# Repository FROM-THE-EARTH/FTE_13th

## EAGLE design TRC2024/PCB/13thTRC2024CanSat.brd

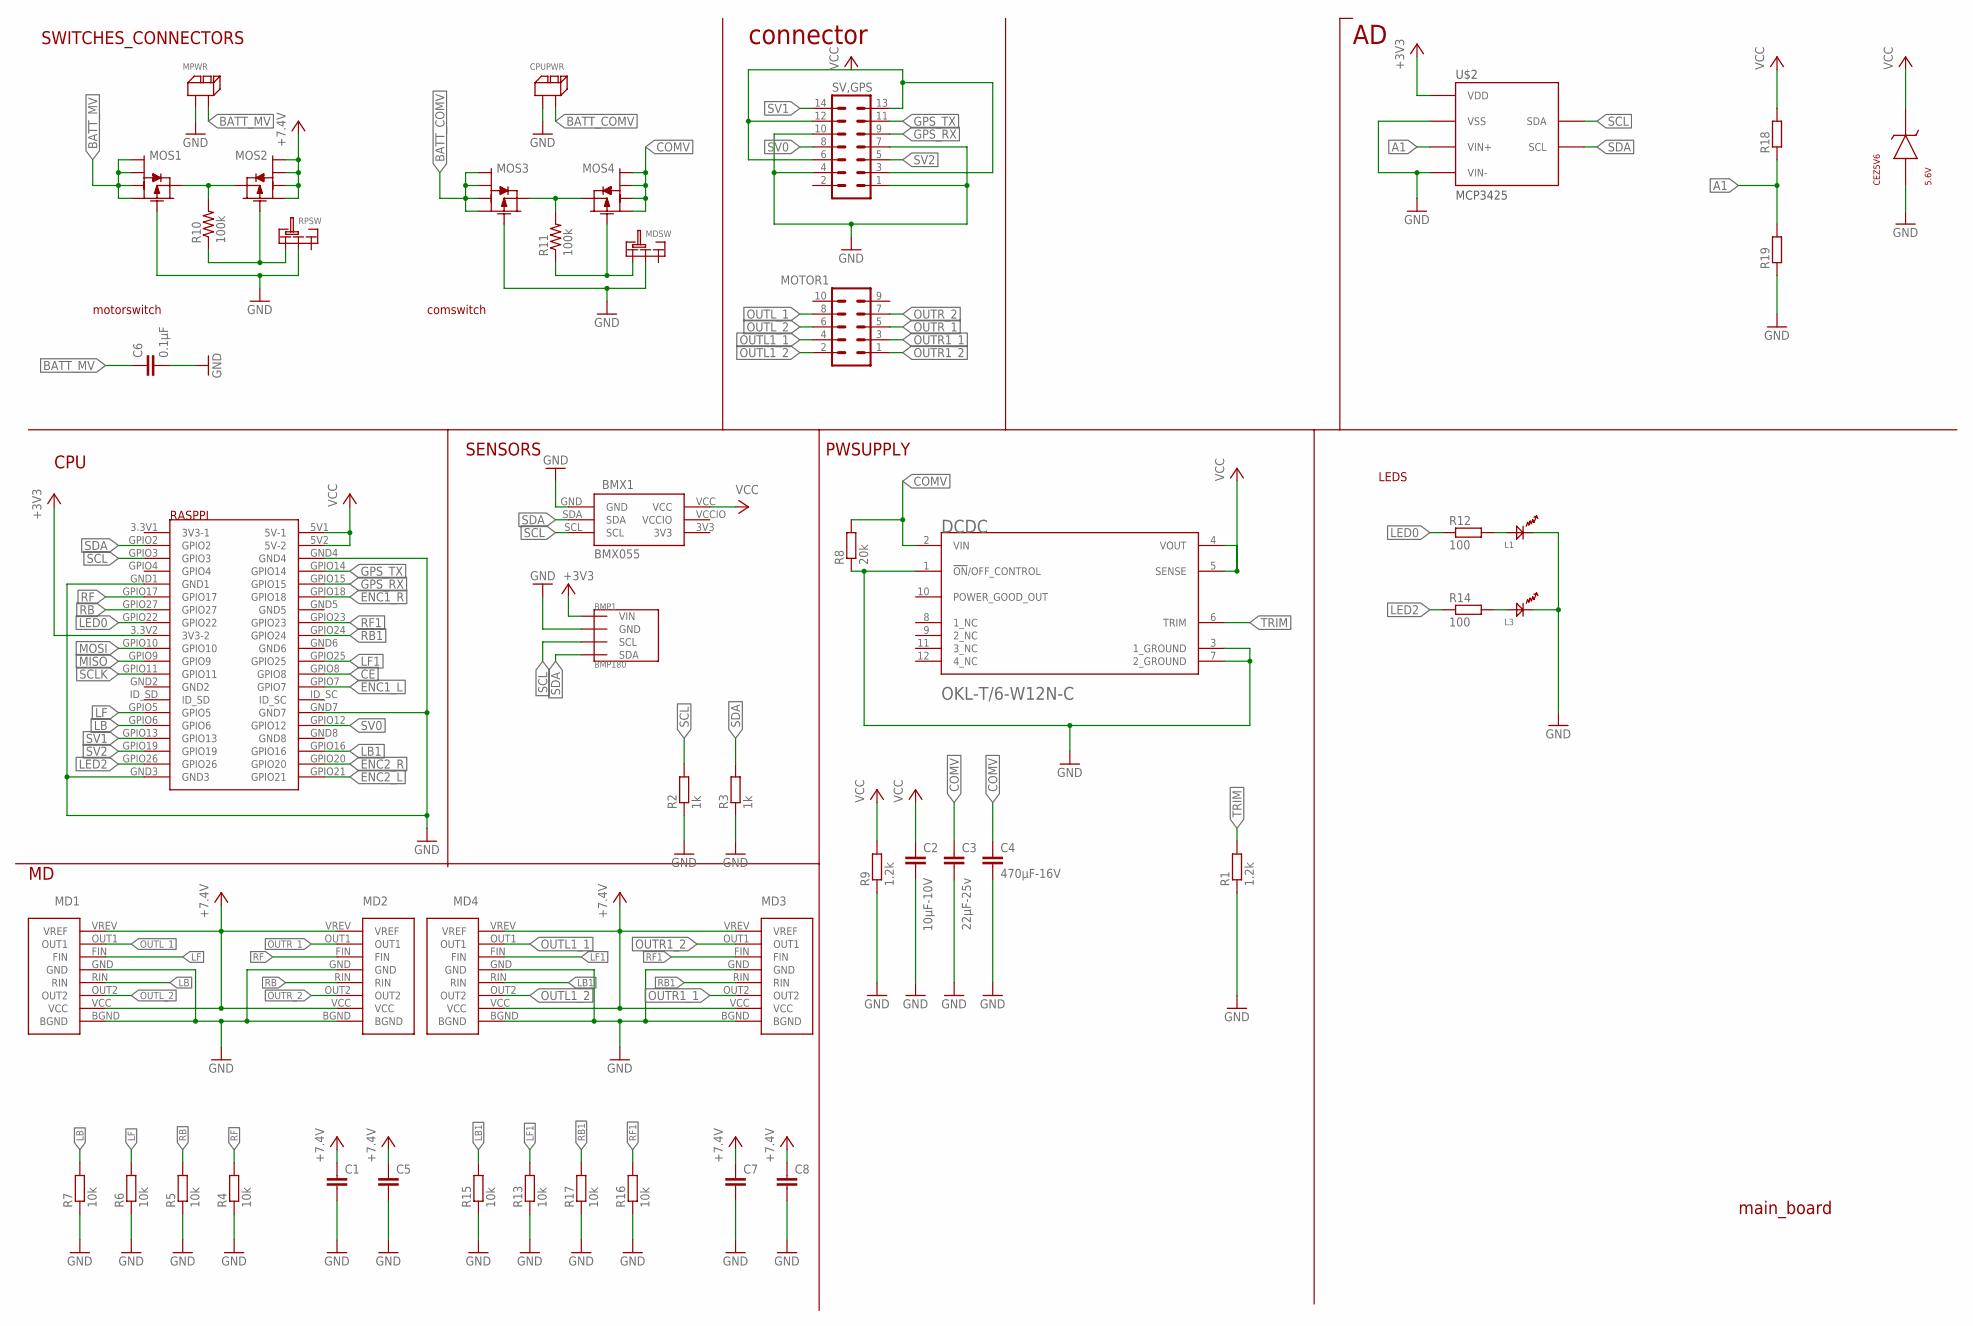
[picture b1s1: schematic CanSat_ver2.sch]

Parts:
BMP1: BMP180; GY-68
BMX1: BMX055
C1, C5, C7, C8: C-EUC0603; C0603
C2: 10μF-10V; C0603
C3: 22μF-25v; C0805
C4: 470μF-16V; C0603
C6: 0.1μF; C0603
CEZ5V6: 5.6V; CEZ5V6
CPUPWR: 2PIN
DCDC: OKL-T/6-W12N-CMURATA_OKL-T-6-W12N-C_0_0; MURATA_OKL-T-6-W12N-C_0
L1, L3: OSXX1608C1A
MD1, MD2, MD3, MD4: BD6222HFP-TR
MDSW: SRIDE_SWITCH
MOS1, MOS2, MOS3, MOS4: PCH_SSM6J808R; SSM6J808R
MOTOR1: ML10L
MPWR: 2PIN
R1, R9: 1.2k; R0805
R2, R3: 1k; R0603
R4, R5, R6, R7, R13, R15, R16, R17: 10k; R0603
R8: 20k; R0603
R10, R11: 100k; R0603
R12, R14: 100; R0603
R18, R19: R-EU_R0603; R0603
RASPPI: RASPBERYPIZEROW
RPSW: SRIDE_SWITCH
SV,GPS: ML14L
U$2: MCP3425; SOT23-6

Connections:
3V3: BMX1.3V3
+3V3: BMP1.P1 (VIN), RASPPI.3.3V2 (3V3-2), U$2.5 (VDD)
+5V: C1.1, C5.1, C7.1, C8.1, MD1.VCC, MD1.VREV (VREF), MD2.VCC, MD2.VREV (VREF), MD3.VCC, MD3.VREV (VREF), MD4.VCC, MD4.VREV (VREF), MOS2.1, MOS2.2, MOS2.5, MOS2.6
A1: R18.1, R19.2, U$2.1 (VIN+)
BATT_COMV: CPUPWR.P$2, MOS3.1, MOS3.2, MOS3.5, MOS3.6
BATT_MV: C6.1, MOS1.1, MOS1.2, MOS1.5, MOS1.6, MPWR.P$2
CE: RASPPI.GPIO8
COMV: C3.1, C4.1, DCDC.2 (VIN), MOS4.1, MOS4.2, MOS4.5, MOS4.6, R8.2
ENC1_L: RASPPI.GPIO7
ENC1_R: RASPPI.GPIO18
ENC2_L: RASPPI.GPIO21
ENC2_R: RASPPI.GPIO20
GND: BMP1.P2 (GND), BMX1.GND, C1.2, C2.2, C3.2, C4.2, C5.2, C6.2, C7.2, C8.2, CEZ5V6.P$1, CPUPWR.P$1, DCDC.1 (!ON!/OFF_CONTROL), DCDC.3 (1_GROUND), DCDC.7 (2_GROUND), L1.CT, L3.CT, MD1.BGND, MD1.GND, MD2.BGND, MD2.GND, MD3.BGND, MD3.GND, MD4.BGND, MD4.GND, MDSW.LR, MOS1.3, MOS3.3, MPWR.P$1, R1.1, R2.1, R3.1, R4.1, R5.1, R6.1, R7.1, R8.1, R9.1, R13.1, R15.1, R16.1, R17.1, R19.1, RASPPI.GND1, RASPPI.GND3, RASPPI.GND4, RASPPI.GND7, RPSW.LR, SV,GPS.1, SV,GPS.4, SV,GPS.7, SV,GPS.10; also elsewhere on the board
GPS_RX: RASPPI.GPIO15, SV,GPS.9; also elsewhere on the board
GPS_TX: RASPPI.GPIO14, SV,GPS.11; also elsewhere on the board
LB: MD1.RIN, R7.2, RASPPI.GPIO6
LB1: MD4.RIN, R15.2, RASPPI.GPIO16
LED2: R14.1, RASPPI.GPIO26
LF: MD1.FIN, R6.2, RASPPI.GPIO5
LF1: MD4.FIN, R13.2, RASPPI.GPIO25
MISO: RASPPI.GPIO9
MOSI: RASPPI.GPIO10
unnamed: MOS3.4, MOS4.4, R11.2
unnamed: MDSW.L, MOS4.3, R11.1
unnamed: L1.AN, R12.2
unnamed: L3.AN, R14.2
unnamed: MOS1.4, MOS2.4, R10.2
unnamed: MOS2.3, R10.1, RPSW.L
OUTL1_1: MD4.OUT1, MOTOR1.4
OUTL1_2: MD4.OUT2, MOTOR1.2
OUTL_1: MD1.OUT1, MOTOR1.8
OUTL_2: MD1.OUT2, MOTOR1.6
OUTR1_1: MD3.OUT2, MOTOR1.3
OUTR1_2: MD3.OUT1, MOTOR1.1
OUTR_1: MD2.OUT1, MOTOR1.5
OUTR_2: MD2.OUT2, MOTOR1.7
RB: MD2.RIN, R5.2, RASPPI.GPIO27
RB1: MD3.RIN, R17.2, RASPPI.GPIO24
RF: MD2.FIN, R4.2, RASPPI.GPIO17
RF1: MD3.FIN, R16.2, RASPPI.GPIO23
SCL: BMP1.P3 (SCL), BMX1.SCL, R2.2, RASPPI.GPIO3, U$2.4 (SDA)
SCLK: RASPPI.GPIO11
SDA: BMP1.P4 (SDA), BMX1.SDA, R3.2, RASPPI.GPIO2, U$2.3 (SCL)
SV0: RASPPI.GPIO12, SV,GPS.8
SV1: RASPPI.GPIO13, SV,GPS.14; also elsewhere on the board
TRIM: DCDC.6 (TRIM), R1.2
VCC: BMX1.VCC, C2.1, CEZ5V6.P$2, DCDC.4 (VOUT), DCDC.5 (SENSE), R9.2, R18.2, RASPPI.5V1 (5V-1), RASPPI.5V2 (5V-2), SV,GPS.3, SV,GPS.6, SV,GPS.12, SV,GPS.13; also elsewhere on the board
VCCIO: BMX1.VCCIO
VSS: U$2.2 (VSS), U$2.6 (VIN-)

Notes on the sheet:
CPU
SENSORS
PWSUPPLY
SWITCHES_CONNECTORS
main_board
motorswitch
comswitch
LEDS
connector

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
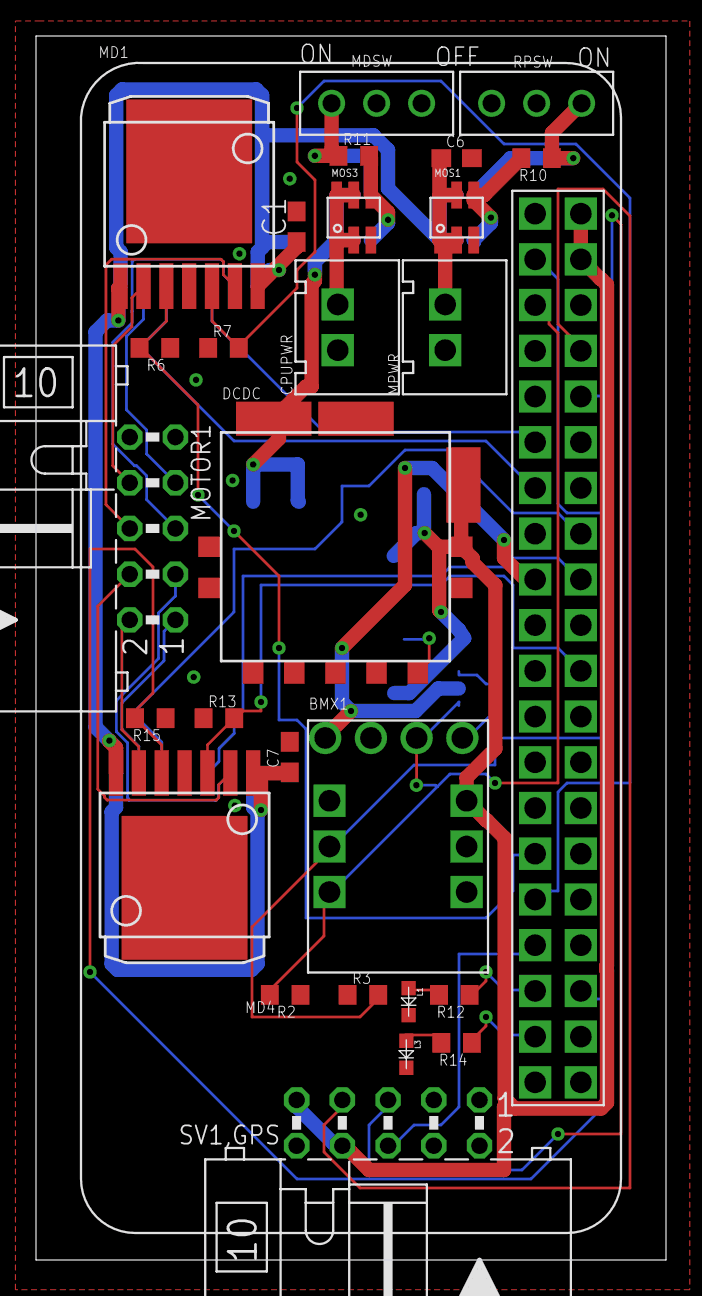
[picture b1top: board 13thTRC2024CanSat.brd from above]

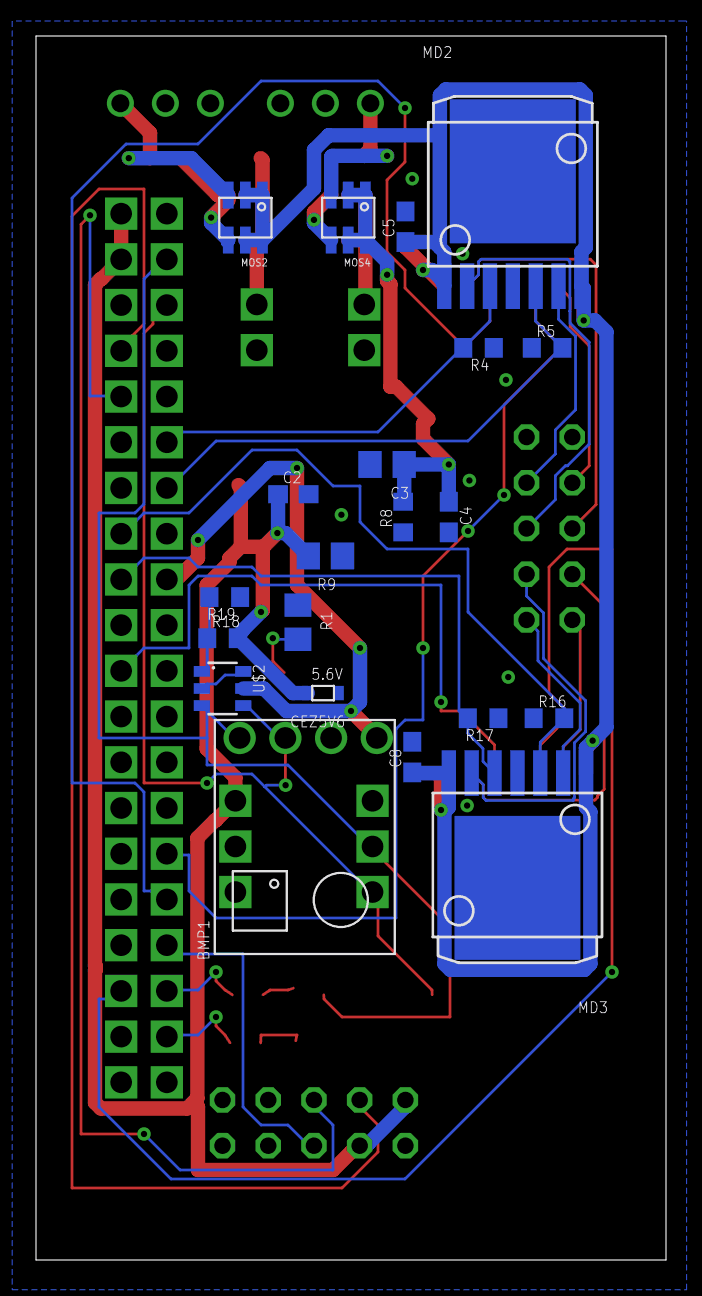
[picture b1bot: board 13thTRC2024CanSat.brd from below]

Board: 2 copper layers, 35.0 x 68.0 mm, 49 parts (21 on the bottom side), 39 nets.

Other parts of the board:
SV1,GPS: ML10L

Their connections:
GND: SV1,GPS.3, SV1,GPS.4; also elsewhere on the board
GPS_RX: SV1,GPS.5; also elsewhere on the board
GPS_TX: SV1,GPS.7; also elsewhere on the board
SV1: SV1,GPS.6; also elsewhere on the board
VCC: SV1,GPS.8, SV1,GPS.9; also elsewhere on the board

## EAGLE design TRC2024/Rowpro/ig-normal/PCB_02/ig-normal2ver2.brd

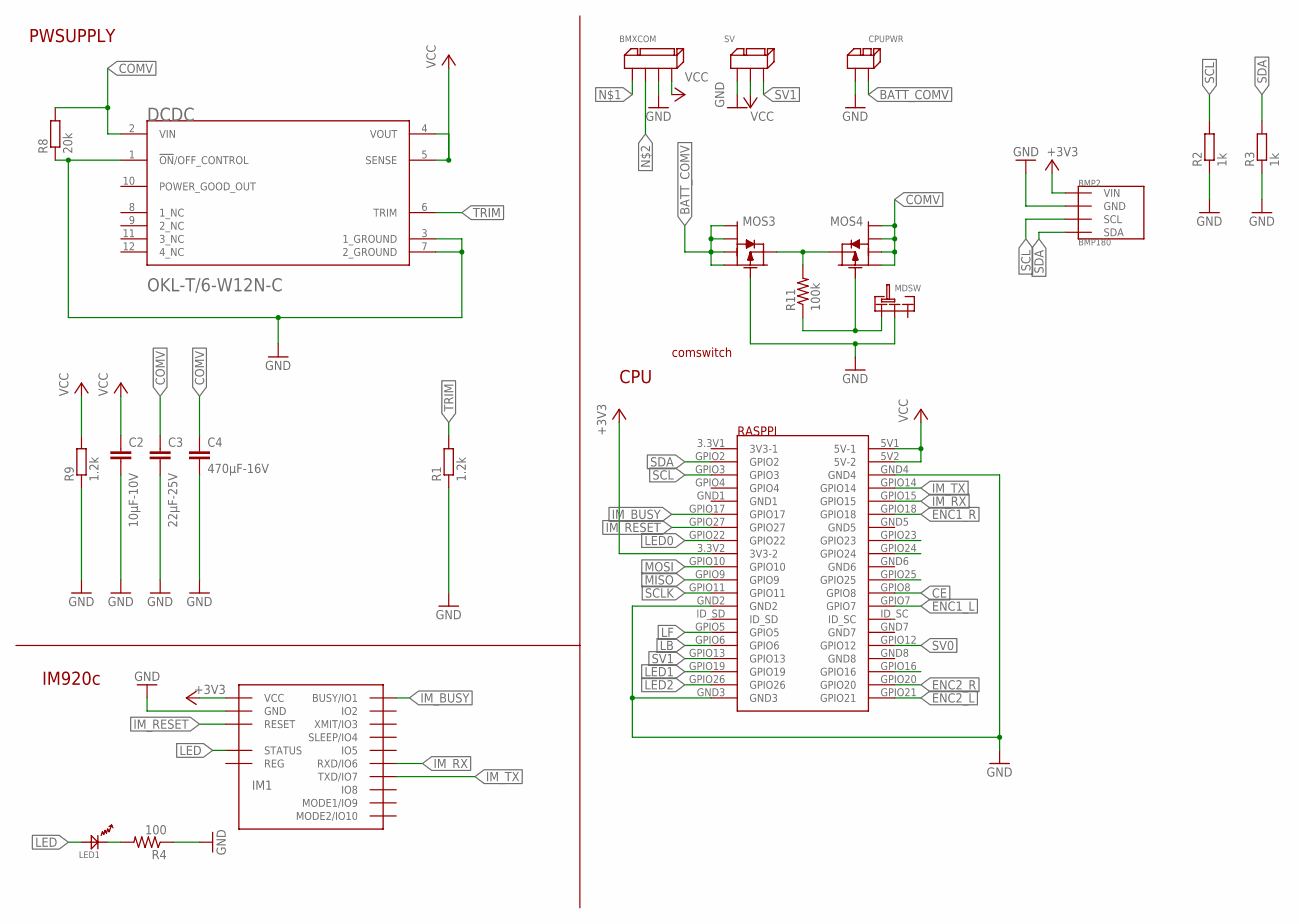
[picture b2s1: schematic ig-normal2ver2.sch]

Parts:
BMP2: BMP180; GY-68
BMXCOM: 4PIN
C2: 10μF-10V; C0603
C3: 22μF-25V; C0603
C4: 470μF-16V; C0603
CPUPWR: 2PIN
DCDC: OKL-T/6-W12N-CMURATA_OKL-T-6-W12N-C_0_0; MURATA_OKL-T-6-W12N-C_0
IM1: IM920_IM920C
LED1: OSXX1608C1A
MDSW: SRIDE_SWITCH
MOS3, MOS4: PCH_SSM6J808R; SSM6J808R
R1, R9: 1.2k; R0805
R2, R3: 1k; R0603
R4: 100; R0603
R8: 20k; R0603
R11: 100k; R0603
RASPPI: RASPBERYPIZEROW
SV: 3PIN

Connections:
+3V3: BMP2.P1 (VIN), IM1.$P17 (VCC), RASPPI.3.3V2 (3V3-2)
BATT_COMV: CPUPWR.P$2, MOS3.1, MOS3.2, MOS3.5, MOS3.6
CE: RASPPI.GPIO8
COMV: C3.1, C4.1, DCDC.2 (VIN), MOS4.1, MOS4.2, MOS4.5, MOS4.6, R8.2
ENC1_L: RASPPI.GPIO7
ENC1_R: RASPPI.GPIO18
ENC2_L: RASPPI.GPIO21
ENC2_R: RASPPI.GPIO20
GND: BMP2.P2 (GND), BMXCOM.P$3, C2.2, C3.2, C4.2, CPUPWR.P$1, DCDC.1 (!ON!/OFF_CONTROL), DCDC.3 (1_GROUND), DCDC.7 (2_GROUND), IM1.$P18 (GND), MDSW.LR, MOS3.3, R1.1, R2.1, R3.1, R4.1, R8.1, R9.1, RASPPI.GND2, RASPPI.GND3, RASPPI.GND4, SV.P$1
IM_BUSY: IM1.$P1 (BUSY/IO1), RASPPI.GPIO17
IM_RESET: IM1.$P19 (RESET), RASPPI.GPIO27
IM_RX: IM1.$P6 (RXD/IO6), RASPPI.GPIO15
IM_TX: IM1.$P7 (TXD/IO7), RASPPI.GPIO14
LB: RASPPI.GPIO6
LB1: RASPPI.GPIO16
LED: IM1.$P15 (STATUS), LED1.AN
LED0: RASPPI.GPIO22
LED1: RASPPI.GPIO19
LED2: RASPPI.GPIO26
LF: RASPPI.GPIO5
LF1: RASPPI.GPIO25
MISO: RASPPI.GPIO9
MOSI: RASPPI.GPIO10
unnamed: LED1.CT, R4.2
unnamed: MOS3.4, MOS4.4, R11.2
unnamed: MDSW.L, MOS4.3, R11.1
RB1: RASPPI.GPIO24
RF1: RASPPI.GPIO23
SCL: BMP2.P3 (SCL), R2.2, RASPPI.GPIO3
SCLK: RASPPI.GPIO11
SDA: BMP2.P4 (SDA), R3.2, RASPPI.GPIO2
SV0: RASPPI.GPIO12
SV1: RASPPI.GPIO13, SV.P$3
TRIM: DCDC.6 (TRIM), R1.2
VCC: BMXCOM.P$4, C2.1, DCDC.4 (VOUT), DCDC.5 (SENSE), R9.2, RASPPI.5V1 (5V-1), RASPPI.5V2 (5V-2), SV.P$2

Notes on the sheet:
IM920c
PWSUPPLY
comswitch
CPU

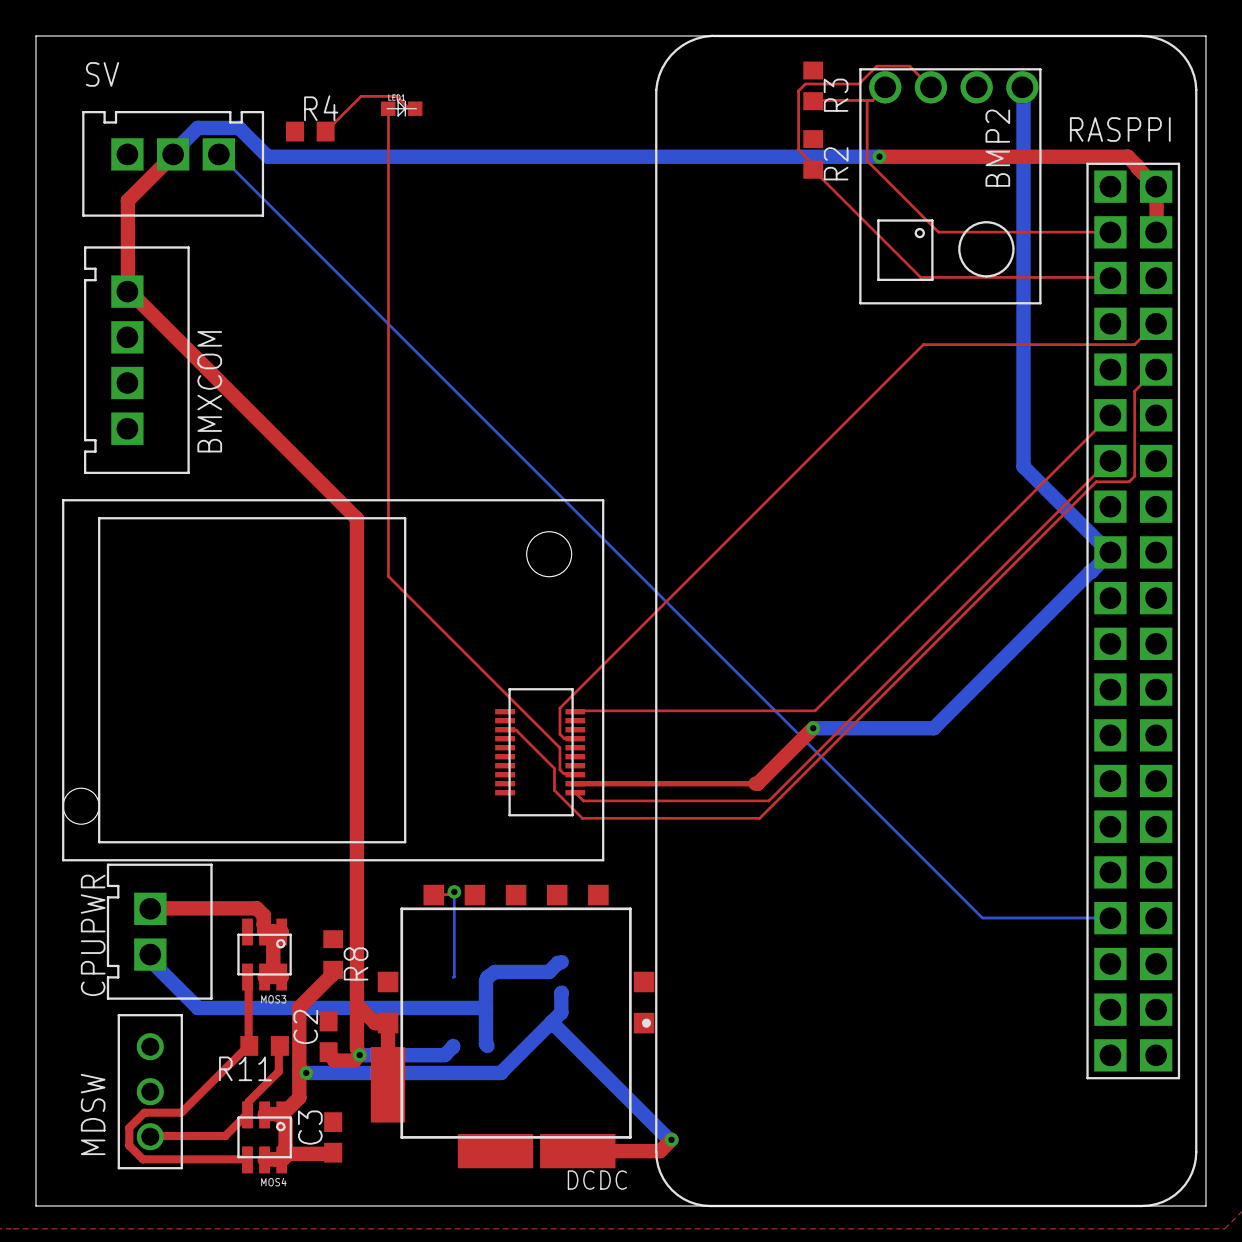
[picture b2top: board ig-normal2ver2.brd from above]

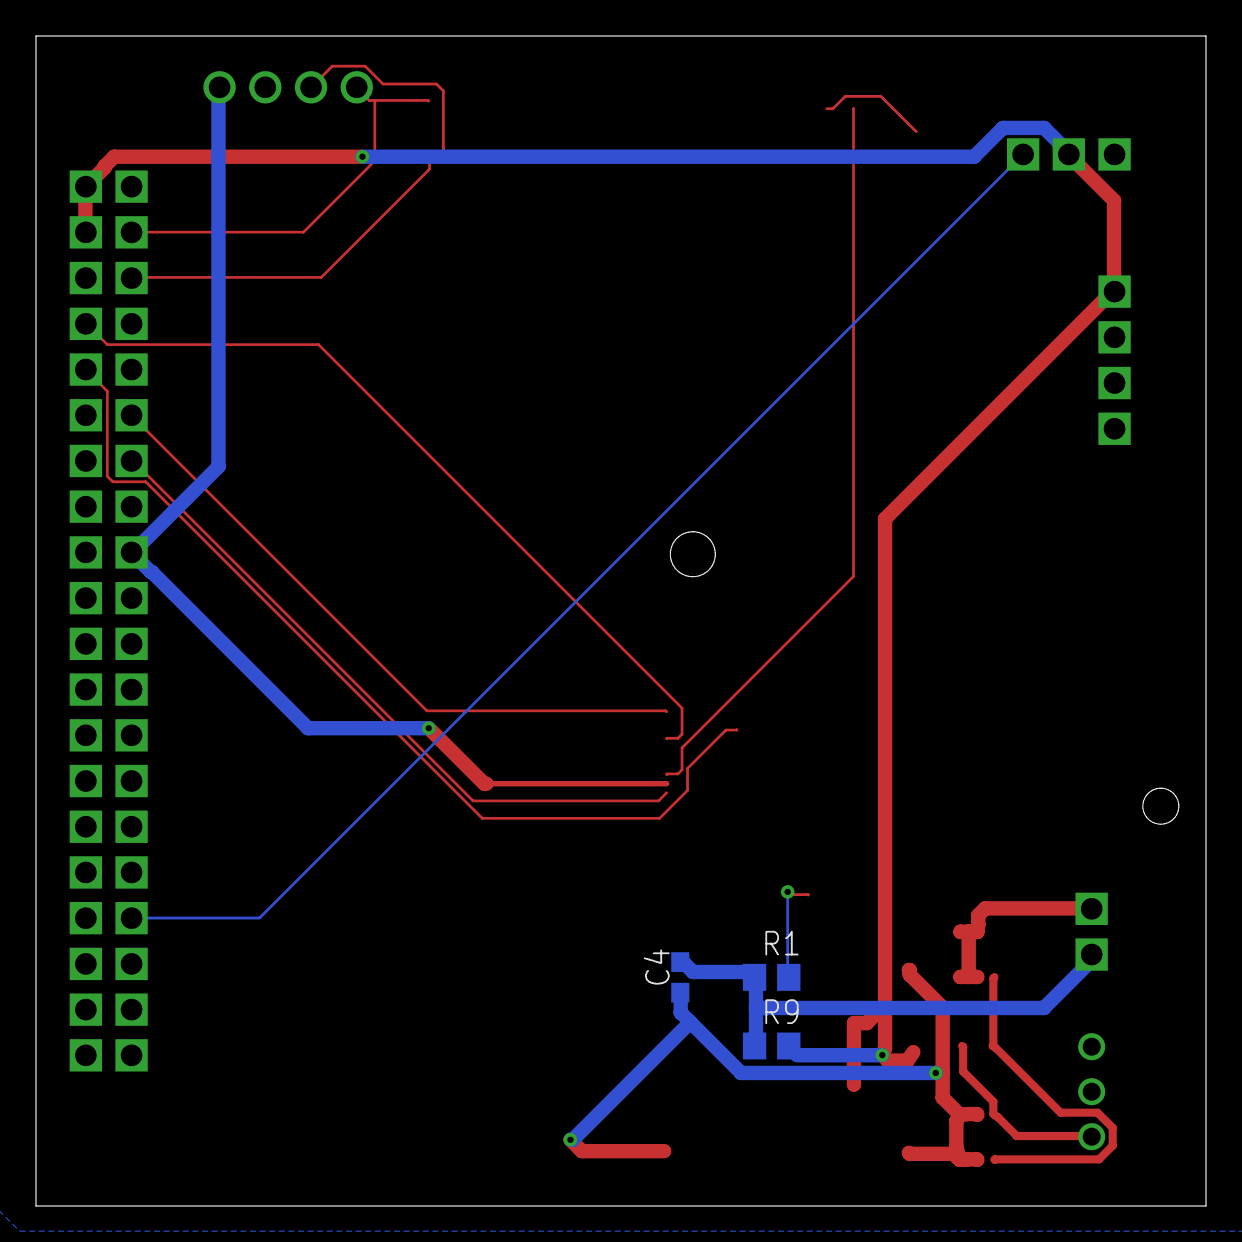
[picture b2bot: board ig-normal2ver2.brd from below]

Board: 2 copper layers, 65.0 x 65.0 mm, 21 parts (3 on the bottom side), 17 nets.
